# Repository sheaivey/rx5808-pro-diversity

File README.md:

# 

This project is a fork of [rx5808-pro](https://code.google.com/p/rx5808-pro/) with support for diversity and much more.

Manufactured version of this project can be found at [La Forge FPV](http://www.laforgefpv.com)

The code is also backward compatible with the original rx5808-pro schematic minus diversity, dip switch mode and TV_Out. For details on updating click [here](/docs/diy-arduino-nano.md).

# Table of Contents
1. [Releases](#releases)
2. [Features](#features)
3. [Overview](#overview)
4. [Hardware](#hardware)
5. [Firmware](#firmware)
6. [Contributing](#contributing)
7. [License](#license)

# Releases
The latest release can be found here. [Latest Releases](https://github.com/sheaivey/rx5808-pro-diversity/releases)

# Features
- **User control** - 3 Button navigation, up, down, select.
- **Manual Mode** - Set channel manual
- **Search Mode** - Search next channel based on RSSI
- **Band Scanner** - Print spectrum of all 48 channels
- **Auto Save** - Saves settings after a few seconds of inactivity.
- **Beeper** - Acoustic feedback on important actions
- **RSSI Graph** - Running history of RSSI readings.
- **Diversity** - Receiver select and monitor.
- **Led Status** - Power, button pressed, active antenna.
- **Race Band & L-Band** - Total of 48 supported channels.
- **Backward Compatibility** - Use this code with your existing setup.
- **OLED Display** - Use a 128x64 OLED.
- **Setup Menu** - Creating changing settings (RSSI Calibration).

# Overview
Please watch the following video giving a detailed overview of the latest v2.0 release.

<p align="center">
    
</p>

1. **Auto Scan** - Scans all bands until a signal with good signal strength is found.
2. **Manual Mode** - Will hold on a manually selected channel.
3. **Band Scanner** - Scans all bands and presents them with a signal strength bar graph.
5. **Settings Menu** - Saves last used channel and mode for next power cycle. This is also where you enter RSSI calibration mode.
    1. **Calibrate RSSI** - Calibrate the min and max RSSI values.

#### Initial Setup
When powering on for the first time it is best to calibrate your RSSI modules. No two modules have the same RSSI min and max readings. To calibrate follow these steps below. You can repeat this process as many times as needed.

1. Go to the settings menu and follow the calibrate RSSI steps on the screen.

# Hardware
#### Manufactured
If you are not looking to build your own hardware you can purchase manufactured versions from the following companies.

1. **[La Forge FPV](http://www.laforgefpv.com/vrx-pro)** - VRX-PRO
  - Designed by Shea Ivey
  - All Current Hardware versions.
2. Realacc - rx5808-pro-diversity
  - All current hardware versions.
3. FuriousFPV - True-D
  - V2.0 and earlier

#### DIY

This project is centered around the RX5808 5.8GHz receiver module which can be found at a number of online stores. The original rx5808-pro schematic has been modified to incorporate the diversity setup. Additional LEDs have also been added to show the active receiver.

For more information on specific hardware implementations:

1. [DIY Simple - Arduino Nano](/docs/diy-arduino-nano.md)
1. [DIY Intermediate - Custom Board (T-Box)](/docs/diy-through-hole-board.md)
2. [DIY Advanced - Custom Board](/docs/diy-custom-board.md)
1. [OLED Version - Arduino Nano](/docs/oled-arduino-nano.md)
3. [rx5808 SPI modification](/docs/rx5808-spi-mod.md)
6. [Voltage Monitoring](/docs/voltage-monitoring.md)

# Firmware
The firmware is constantly being improved please refer to the release history for more detailed information on improvements.
[Release History](https://github.com/sheaivey/rx5808-pro-diversity/releases)

# Contributing
Any contributions are welcome!

Please follow [CONTRIBUTING.md](CONTRIBUTING.md) for standard practices regarding this repo.

## Recognition
- SPI driver based on fs_skyrf_58g-main.c Written by Simon Chambers
- TVOUT by Myles Metzel
- Scanner by Johann Hermen (der-Frickler.net)
- Initial 2 Button version by Peter (pete1990)
- Refactored and GUI reworked by Marko Hoepken
- Universal version my Marko Hoepken
- Diversity Receiver Board and GUI improvements by Shea Ivey
- Adding Race Band by Shea Ivey
- Separating Display concerns for TVOut and OLED by Shea Ivey
- Adding Setup Menu by Shea Ivey
- DIY Throughole board and documentation. by RCDaddy
- Voltage monitoring by kabturek
- v2.0 Firmware Overhaul by @Knifa

# License
## Code
The code is distrubuted under the [MIT license](LICENSE.md).

## Logo
The logo is distributed under the [Creative Commons Attribution 4.0 International](http://creativecommons.org/licenses/by/4.0/) license.

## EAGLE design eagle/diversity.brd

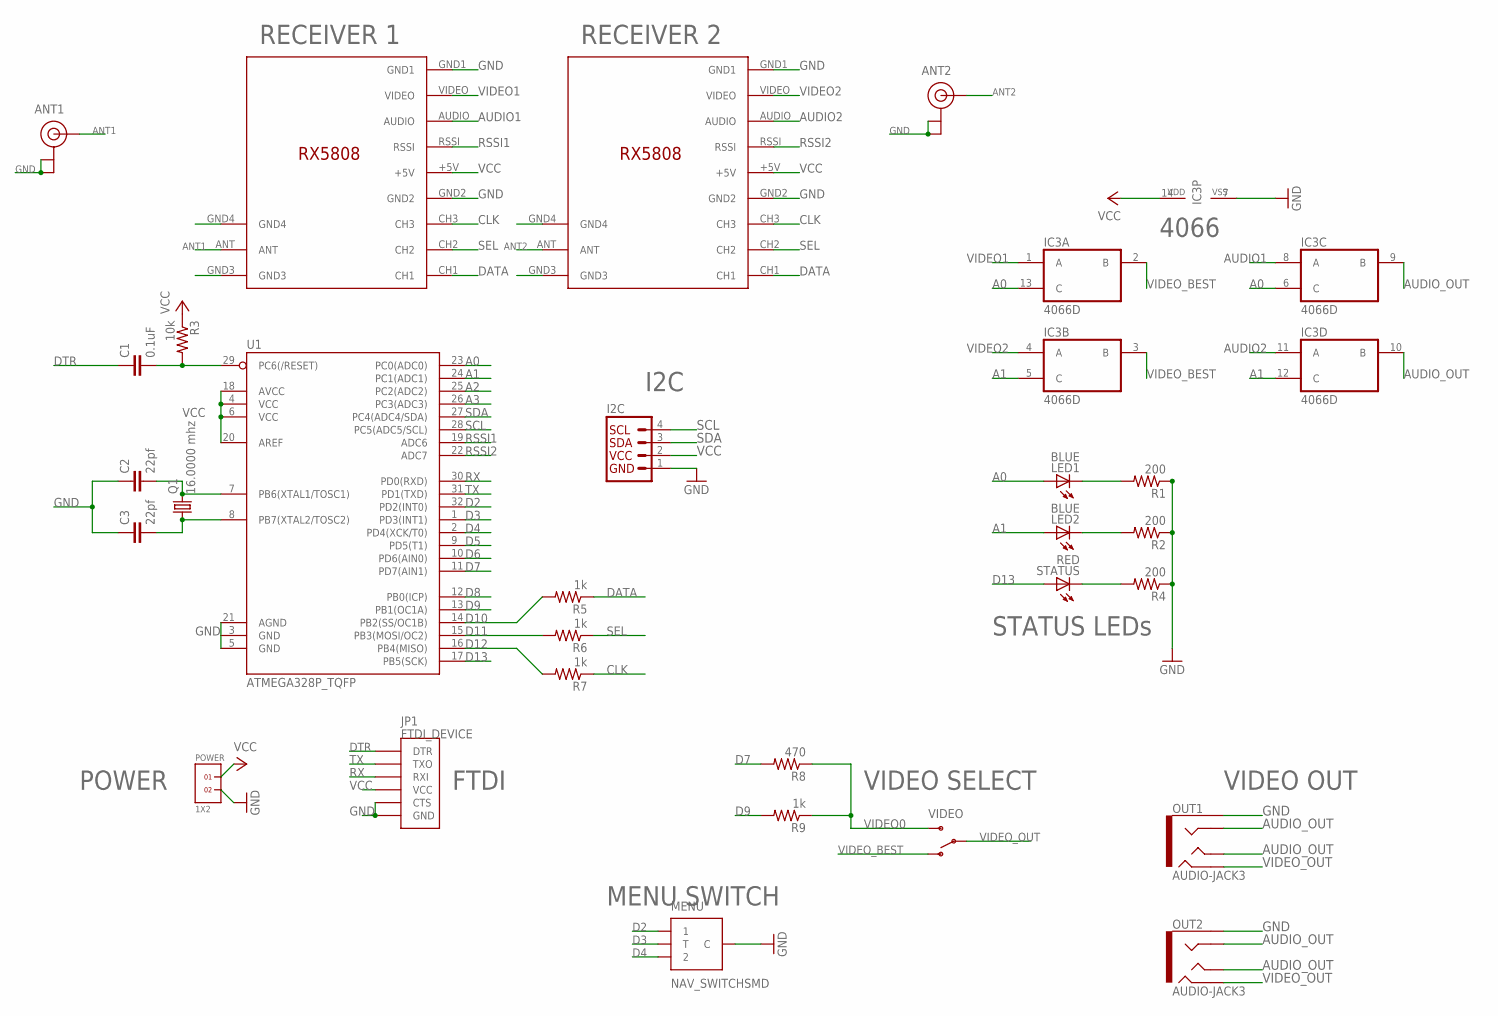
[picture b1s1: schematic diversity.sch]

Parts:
ANT1, ANT2: U.FL
C1: 0.1uF; 0603-CAP
C2, C3: 22pf; 0603-CAP
I2C: I2C_STANDARD; 1X04
IC3: 4066D; SO14
JP1: FTDI_DEVICE; FTDI_DEVICE_SIDE
LED1, LED2: BLUE; SML0603
MENU: NAV_SWITCHSMD; NAV_SWITCH
OUT1, OUT2: AUDIO-JACK3; AUDIO-JACK-TRRS-SMD
POWER: 1X2
Q1: 16.0000 mhz; HC49U-V
R1, R2, R4: 200; R0603
R3: 10k; R0603
R5, R6, R7, R9: 1k; R0603
R8: 470; R0603
RECEIVER_A: RX5808_A; RX5808
RECEIVER_B: RX5808_B; RX5808
STATUS: RED; SML0603
U1: ATMEGA328P_TQFP; TQFP32-08
VIDEO: SWITCH-SPDTSMD2; SWITCH-SPDT-SMD

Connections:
A0: IC3.6 (C), IC3.13 (C), LED1.A, U1.23 (PC0(ADC0))
A1: IC3.5 (C), IC3.12 (C), LED2.A, U1.24 (PC1(ADC1))
A2: U1.25 (PC2(ADC2))
A3: U1.26 (PC3(ADC3))
ANT1: ANT1.P$3 (SIGNAL), RECEIVER_A.ANT
ANT2: ANT2.P$3 (SIGNAL), RECEIVER_B.ANT
AUDIO1: IC3.8 (A), RECEIVER_A.AUDIO
AUDIO2: IC3.11 (A), RECEIVER_B.AUDIO
AUDIO_OUT: IC3.9 (B), IC3.10 (B), OUT1.RING1, OUT1.TIP, OUT2.RING1, OUT2.TIP
CLK: R7.1, RECEIVER_A.CH3, RECEIVER_B.CH3
D2: MENU.1, U1.32 (PD2(INT0))
D3: MENU.T, U1.1 (PD3(INT1))
D4: MENU.2, U1.2 (PD4(XCK/T0))
D5: U1.9 (PD5(T1))
D6: U1.10 (PD6(AIN0))
D7: R8.2, U1.11 (PD7(AIN1))
D8: U1.12 (PB0(ICP))
D9: R9.2, U1.13 (PB1(OC1A))
D10: R5.2, U1.14 (PB2(SS/OC1B))
D11: R6.2, U1.15 (PB3(MOSI/OC2))
D12: R7.2, U1.16 (PB4(MISO))
D13: STATUS.A, U1.17 (PB5(SCK))
DATA: R5.1, RECEIVER_A.CH1, RECEIVER_B.CH1
DTR: C1.1, JP1.P$1 (DTR)
GND: ANT1.P$1 (GND), ANT1.P$2 (GND), ANT2.P$1 (GND), ANT2.P$2 (GND), C2.1, C3.1, I2C.1, IC3.7 (VSS), JP1.P$5 (CTS), JP1.P$6 (GND), MENU.C, OUT1.EARTH, OUT2.EARTH, POWER.2, R1.1, R2.1, R4.1, RECEIVER_A.GND1, RECEIVER_A.GND2, RECEIVER_A.GND3, RECEIVER_A.GND4, RECEIVER_B.GND1, RECEIVER_B.GND2, RECEIVER_B.GND3, RECEIVER_B.GND4, U1.5 (GND), U1.21 (AGND)
unnamed: LED1.C, R1.2
unnamed: LED2.C, R2.2
unnamed: C2.2, Q1.2, U1.7 (PB6(XTAL1/TOSC1))
unnamed: C1.2, R3.2, U1.29 (PC6(/RESET))
unnamed: C3.2, Q1.1, U1.8 (PB7(XTAL2/TOSC2))
unnamed: R4.2, STATUS.C
RSSI1: RECEIVER_A.RSSI, U1.19 (ADC6)
RSSI2: RECEIVER_B.RSSI, U1.22 (ADC7)
RX: JP1.P$3 (RXI), U1.30 (PD0(RXD))
SCL: I2C.4, U1.28 (PC5(ADC5/SCL))
SDA: I2C.3, U1.27 (PC4(ADC4/SDA))
SEL: R6.1, RECEIVER_A.CH2, RECEIVER_B.CH2
TX: JP1.P$2 (TXO), U1.31 (PD1(TXD))
VCC: I2C.2, IC3.14 (VDD), JP1.P$4 (VCC), POWER.1, R3.1, RECEIVER_A.+5V, RECEIVER_B.+5V, U1.4 (VCC), U1.6 (VCC), U1.18 (AVCC), U1.20 (AREF)
VIDEO0: R8.1, R9.1, VIDEO.3 (S)
VIDEO1: IC3.1 (A), RECEIVER_A.VIDEO
VIDEO2: IC3.4 (A), RECEIVER_B.VIDEO
VIDEO_BEST: IC3.2 (B), IC3.3 (B), VIDEO.1 (O)
VIDEO_OUT: OUT1.RING2, OUT2.RING2, VIDEO.2

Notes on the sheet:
POWER
FTDI
RECEIVER 1
RECEIVER 2
4066
STATUS LEDs
I2C
MENU SWITCH
VIDEO OUT
VIDEO SELECT

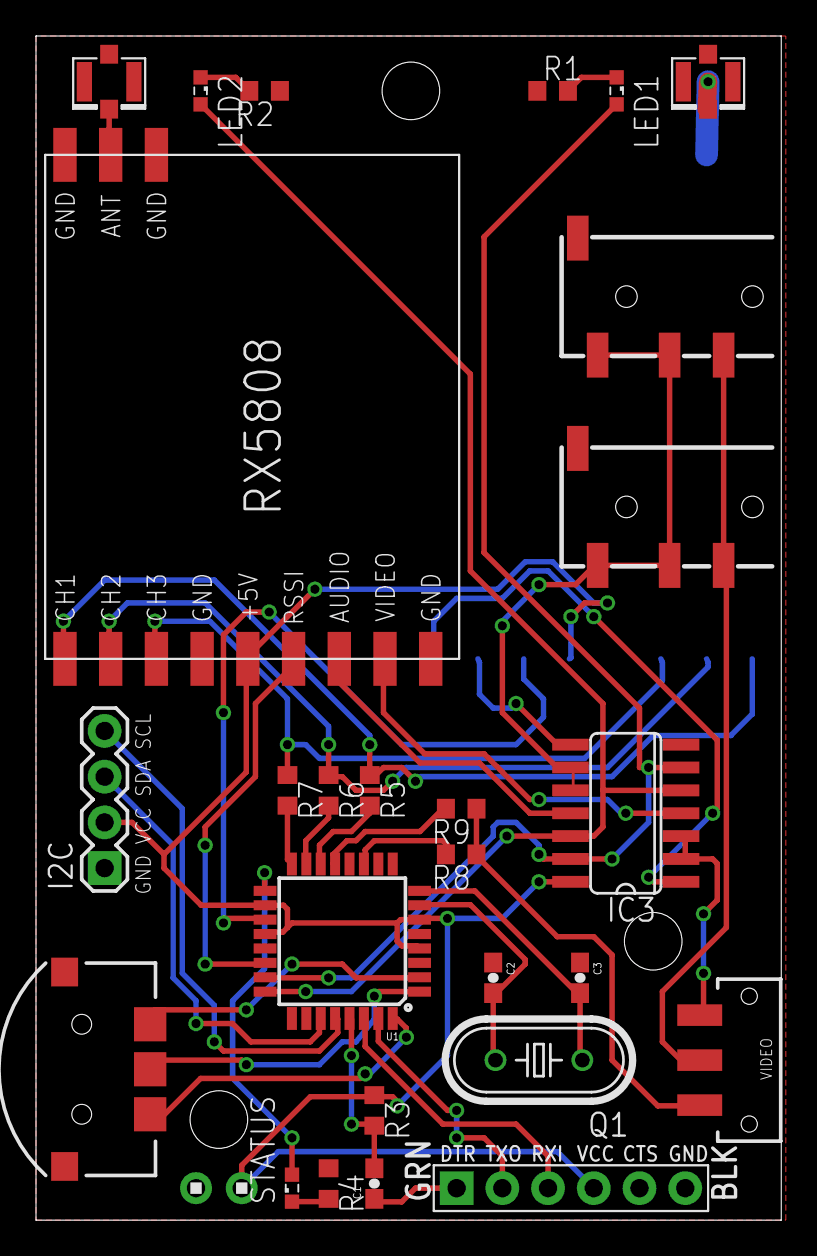
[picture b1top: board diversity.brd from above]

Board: 2 copper layers, 41.4 x 65.8 mm, 29 parts (1 on the bottom side), 39 nets.

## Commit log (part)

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2015-08-30 Adding screen shots of the OLED version.
2015-08-30 updating old docs to include what source code to use.
2015-08-31 making menu title consistent with TV_OUT
2015-09-01 Fixing minor GUI redrawing issues.
2015-09-02 Updating documentation to include proper OLED initialization with the Adafruit library.
2015-09-02 removing unnecessary files from project. Will replace with OSH Park open hardware links.
2015-09-03 adding oled video to documentation.
2015-09-03 Adding new screen saver feature when idle. Shows Channel and call sign along with RSSI.
2015-09-03 Adding screen saver to OLED screens.
2015-09-05 Adding RSSI_READS - number of analog reads per RSSI check. Increasing RSSI_READS to 50. Gives a better average.
2015-09-06 Updating low signal to blink.
2015-09-07 Bad PR... Not sure how this got back into the mix.
2015-09-08 speeding up screensaver refresh rate.
2015-09-09 updating custom board documentation.
2015-09-09 adding new example install to 7" monitor.
2015-09-10 Adding optional I2C and Buzzer to the board.
2015-09-12 Fixes errors when not in diversity mode
2015-09-13 Cleaning up error when not using diversity.
2015-09-13 Finished ScreenSaver
2015-09-14 Finishing adafruit screens. Starting on TVOut screens.
2015-09-14 Working on TVOut_screens
2015-09-15 Just screen saver remaining.
2015-09-16 adding header to settings.
2015-09-16 fixing best list in band scan mode.
2015-09-16 setting TVOut as default screen.
2015-09-21 Delays should be handled by wait_rssi_ready().
2015-09-21 fixing ordered list.
2015-09-30 Auto detect diversity module #34
2015-10-01 After each seek recalculate the seek lock threshold. When returning from band scan set channel to users saved channel.
2015-10-02 Getting ready for Setup Menu
2015-10-03 adding setup menu
2015-10-03 saving settings to eeprom call sign beeps scan order updating ui
2015-10-05 adding pull down resistor to RSSI
2015-10-22 Adding LICENSE to the project.
2015-10-22 Defaulting project to OLED due to its popularity.
2015-10-23 Rename diy-through-hole-boardv1.1.md to diy-through-hole-board-v1.1.md
2015-10-25 First final version to merge.
2015-10-26 Revert "Update to diy-through-hole-boardv1.1.md"
    This reverts commit ffe85fbc083b51d936229bd0ebec730301b6fc76.
2015-10-27 Adding recognision to RCDaddy for his through hole version of the board.
2015-10-27 updating url
2015-10-27 Update diy-through-hole-board.md
    Added code change for atmega328p.
2015-10-28 removing unused debug feature.
2015-10-28 transmit channel and callsign in manual mode and on a channel with a low signal
2015-11-03 don't change to screen saver until we have a strong signal. broadcast IR channel while there is a weak signal
2015-11-16 Adding donation button.
2015-11-21 Shorten boot check screen time.
2015-11-21 Force screen saver after 30 seconds of low signal
2015-11-21 adding more feature toggles.
2015-11-21 Change seek directions regardless of locked.
2015-11-21 Show seek position in band scan mode
2015-11-21 Update diy-through-hole-board.md
    Updated OSHPark link for v1.1 to revi 2
2015-12-07 Memory optimisation of TVOut_screens.cpp making further use of PROGMEM library. Tested by confirming each of the menus still function correctly connected to an LCD monitor.
2015-12-12 Additional changes to finish 3 antenna diversity & TVout. LED screen saver updates to implement 3 antenna diversity (not fully tested yet).
2015-12-13 Removed isDiversity checking (dynamic check of RSSI on ch B & C) on everything but calibration
2015-12-19 Switching logic change to explicitly check Rx C
2015-12-20 First rework to enable more than 3 receivers
2015-12-20 Various changes to correct RSSI reading & diversity menu display corrected. Screen saver timeout reduced.
2015-12-23 -Removed USE_DIVERSITY pre proc -Receiver numbering now starts from 0 (to make array indexing consistent) -useDiversityAuto now above receivers range -Added display of call sign back in as an option
2015-12-24 Increased the tune time from 25mS to 35mS to allow for stable readings during Cal
2015-12-24 adding INVERT to display commands
2015-12-24 force receiver A when diversity has been disconnected.
2015-12-24 adding comments.
2015-12-28 Moving MIN_TUNE_TIME to settings.h file. adding defaults for which receiver module is being used.
2015-12-28 Updating calibration steps.
2015-12-29 Fix for constrained RSSI readings before being used to compare best diversity module.
2015-12-29 removing magic numbers inlace of already established DEFINE values.
2015-12-30 Added MIN_TUNE_TIME to settings.h. Updated readRSSI to only map before receiver selection, then constrain on return in line with Shea's latest.
2016-01-13 adding check to set calibration back to default when no VTX is present.
2016-01-27 Moved the pinout configurations under a check for NUM_RXS. Means that only NUM_RXS has to be changed for different number of modules.
2016-03-15 Option for inverted buzzer added for hardware from https://github.com/Virtex7/RX5808
2016-04-15 update mouser urls in custom board
2016-05-03 changed time to wait after startup to enable external screen
2016-05-09 settings for RX5808 from virtex 7
2016-05-28 SH1106 support
2016-08-01 Fix for Raceband 5
    Update for the channelTable for raceband 5
2016-09-02 Update oled_128x64_adafruit_screens.cpp
    Added new band with 8 new channels from 5362 MHz to 5621 MHz.
    Modified screens with width of 5/2 instead of 3 of all vertical bars.
2016-09-06 Use define USE_LBAND in settings.h
    User can choose via #define USE_LBAND in settings.h if he wants to enable the feature of 8 new channels.
    If not there is no difference to the original code with 40 channels.
2016-09-06 Update oled_128x64_adafruit_screens.cpp to use #define USE_LBAND
    User can select via #define USE_LBAND in settings.h if the feature of 8 additional channels will be enabled.
2016-09-29 Update README.md
    Updating recognition.
    Adding my La Forge FPV production product link to the project.
2016-10-13 Fix the rssi table display for TVOUT screens
2016-11-16 fix schematic image
2016-11-16 add voltage monitoring to oled, use A2 by default
2016-11-17 fix swapping buttons when editing thx @error414
2016-11-20 dont use DELAY when using the voltage alarm, add options to customize alarm sounds
    fix menu traverse in voltage menu
2016-12-10 Remove incomplete u8g code
    If people are keen they can grab the files from
    previous git history.
2016-12-10 Add support for boot animations
2016-12-10 Add option for toggling boot check
2016-12-11 Init 72 CH
2016-12-12 use direct port manipulation when switching receivers - toggle the two outputs at once
2016-12-13 anim
2016-12-22 Move OLED address setting to settings.h
2016-12-22 Revert "Use common file define convention"
    This reverts commit dec95bd743d017dfcde5f030863e6efae33f6a3d.
2016-12-22 Clean up OLED selection code to minimise pre-processor checks
2016-12-22 Clean up unused variables in main
2016-12-22 Move settings code into a folder
2016-12-22 Improve setting EEPROM defaults
    - Use magic value to determine if the EEPROM has valid data
    - Break out into it's own function
2016-12-22 Drop SPI/Wire includes (handled by Adafruit libs)
2016-12-22 Simplify EEPROM usage
    - EepromSettings struct now contains all possible settings
    - EepromDefaults contain defaults for easy memcpy (not sure on this)
    - Make use of EEPROM's ability to put/get whole structs
    - General usage now: load() at start of program, change some
    stuff inside, call save().
2016-12-22 Standardise on using 'bool' instead of 'boolean'
2016-12-22 Enable pull-up resistors on RSSI pins
2016-12-22 Drop Adafruit GFX include (provided by OLED lib)
2016-12-22 Add define for specifying PTSR2 buffer size
2016-12-22 Move RSSI functions out to receiver files (breaking)
    This breaks RSSI setup just now pending display
    refactoring!
2016-12-22 Break up setup() function
2016-12-22 Some helpers for button state and bebouncing (yet unused)
2016-12-22 Misc. tidying
2016-12-22 Use Arduino style include-guards, but in caps
2016-12-22 Use namespaces for button state handler
    Who would have thought it was a good idea to put enum literals
    in the same namespace as where you define the namespace?
2016-12-22 Spell receiver properly...
2016-12-23 Namespace Receiver functions
2016-12-23 First pass at implementing new style loop
2016-12-23 Super basic tests of switching state
2016-12-23 Bandscanner working with new state machine!
    - Used bandscanner, not auto scan.
    - Seems much tidier.
2016-12-23 More general work on screensaver state
    - Break out into it's own files
    - Re-add screensaver timeout
2016-12-23 Switch to previous state after screensaver button
2016-12-23 Simplify button debounce a little
    - Make use of shortcutting to avoid millis() call
    - Set state /inside/ update func using reference, little gross but
    seems cleaner in this case.
2016-12-23 Add support for button change hooks
2016-12-23 Fix button presses on manual mode state
2016-12-23 Get auto scan working with new state machine
2016-12-24 Rename LICENSE to include .md for consistency
2016-12-24 Slam that logo on the readme
2016-12-24 Test centering
2016-12-27 Rename headers to be category first
    At least, until fixed to be organised into directories
2017-01-17 Use classes for states instead of plain functions
2017-02-04 correctio faute de frappe
2017-02-16 Output active channel with serial out
2017-02-17 Drop old screen files and add stub work for new UI
2017-02-17 Add handlers for drawing
2017-02-17 First pass on reworked scan screen
2017-02-17 First pass at graph on scan screen.
2017-02-17 Add framerate limiter
2017-02-17 Use long for framerate counter
2017-02-17 Tidy up UI design for scan
2017-02-17 Reduce duplication in channel defs
2017-02-17 Make defining new channels easy
2017-02-17 Tidy up reg defines after use
2017-02-18 Tidy up some defines
2017-02-18 Disable serial logging by default
2017-02-18 Tidy up scan UI a little
2017-02-18 Return to menu from auto state
2017-02-19 Fix dumb off-by-one error with channels
2017-02-19 Break out graph func + misc drawing
2017-02-19 Simplify screensaver
2017-02-19 Improve graph scaling
2017-02-19 Misc tidy up
2017-02-19 Drop call sign in favour of logo
2017-02-19 Bump up recever logging length but reduce time
2017-02-19 Nuke old code
2017-02-19 Allow disabling audio blocks on RX58xxx
2017-02-19 Only need to do one read (+ one fake) for valid RSSI
2017-02-19 Drop manual mode (will integrate into scan)
2017-02-22 Fix include guards to match new filenames
2017-02-22 Add slim mode for state search (commented out)
2017-02-22 Rename onTick to onUpdate etc
2017-02-22 Simplify button state somewhat
2017-02-22 Quick hack at getting manual mode working
2017-02-23 Use PGM strings in menu
2017-02-23 Misc memory optimisation
2017-02-24 Fix wrong diversity indicator on search
2017-02-24 Use shared memory space for states
2017-02-24 Remove anntenas message on RSSI setup
2017-02-24 Tidy up state machine
2017-03-10 Fix broken pin mode settings + use RSSI pullup again
2017-03-11 Move search UI code to seperate file
2017-03-13 Add gitter badge
2017-03-25 Implement fast switching from #98
2017-03-25 Use timer helper for screensaver swap
2017-03-25 Fix broken stuff for non-diversity users
2017-03-25 Tweak RSSI tracking speed/count for better graphs
2017-03-26 Fix dumb typos that break diversity
2017-04-10 Don't scan by default
2017-04-10 Use enums for diversity mode
2017-04-10 Drop unused func
2017-04-10 Shift menu rendering out of the UI helper into the menu state since it's not generic enough
2017-04-10 First pass at abstracting different types of button presses (long, short, holding, etc)
2017-04-16 Move state menu to side and add simple animation
2017-04-16 Use icons for state menu
2017-04-17 Only wait for stable RSSI in search when changing channel
2017-04-17 Improve icons
2017-04-28 Add battery voltage on main TVOut screen
2017-04-29 Make RSSI updates non-blocking
2017-04-29 Auto-save search mode/order
2017-04-29 Add channel auto-saving
2017-05-06 Increase PSTR2 buffer (fix broken calibration)
    - No idea how this didn't cause problems before. Luck?
2017-05-14 fixing release link
2017-05-16 Disable Screensaver for Bandscan
    Hey !
    I used the band scan today for testing. I found that the screensaver is annoying in this mode while I'm working with quads.
    What do you think ?
2017-08-18 Add missing include for SH1106 OLED
    Adding missing include header for the OLED SH1106.

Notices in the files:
parts and their libraries:
SparkFun-DigitalIC: Licensing: Creative Commons ShareAlike 4.0 International - https://creativecommons.org/licenses/by-sa/4.0
